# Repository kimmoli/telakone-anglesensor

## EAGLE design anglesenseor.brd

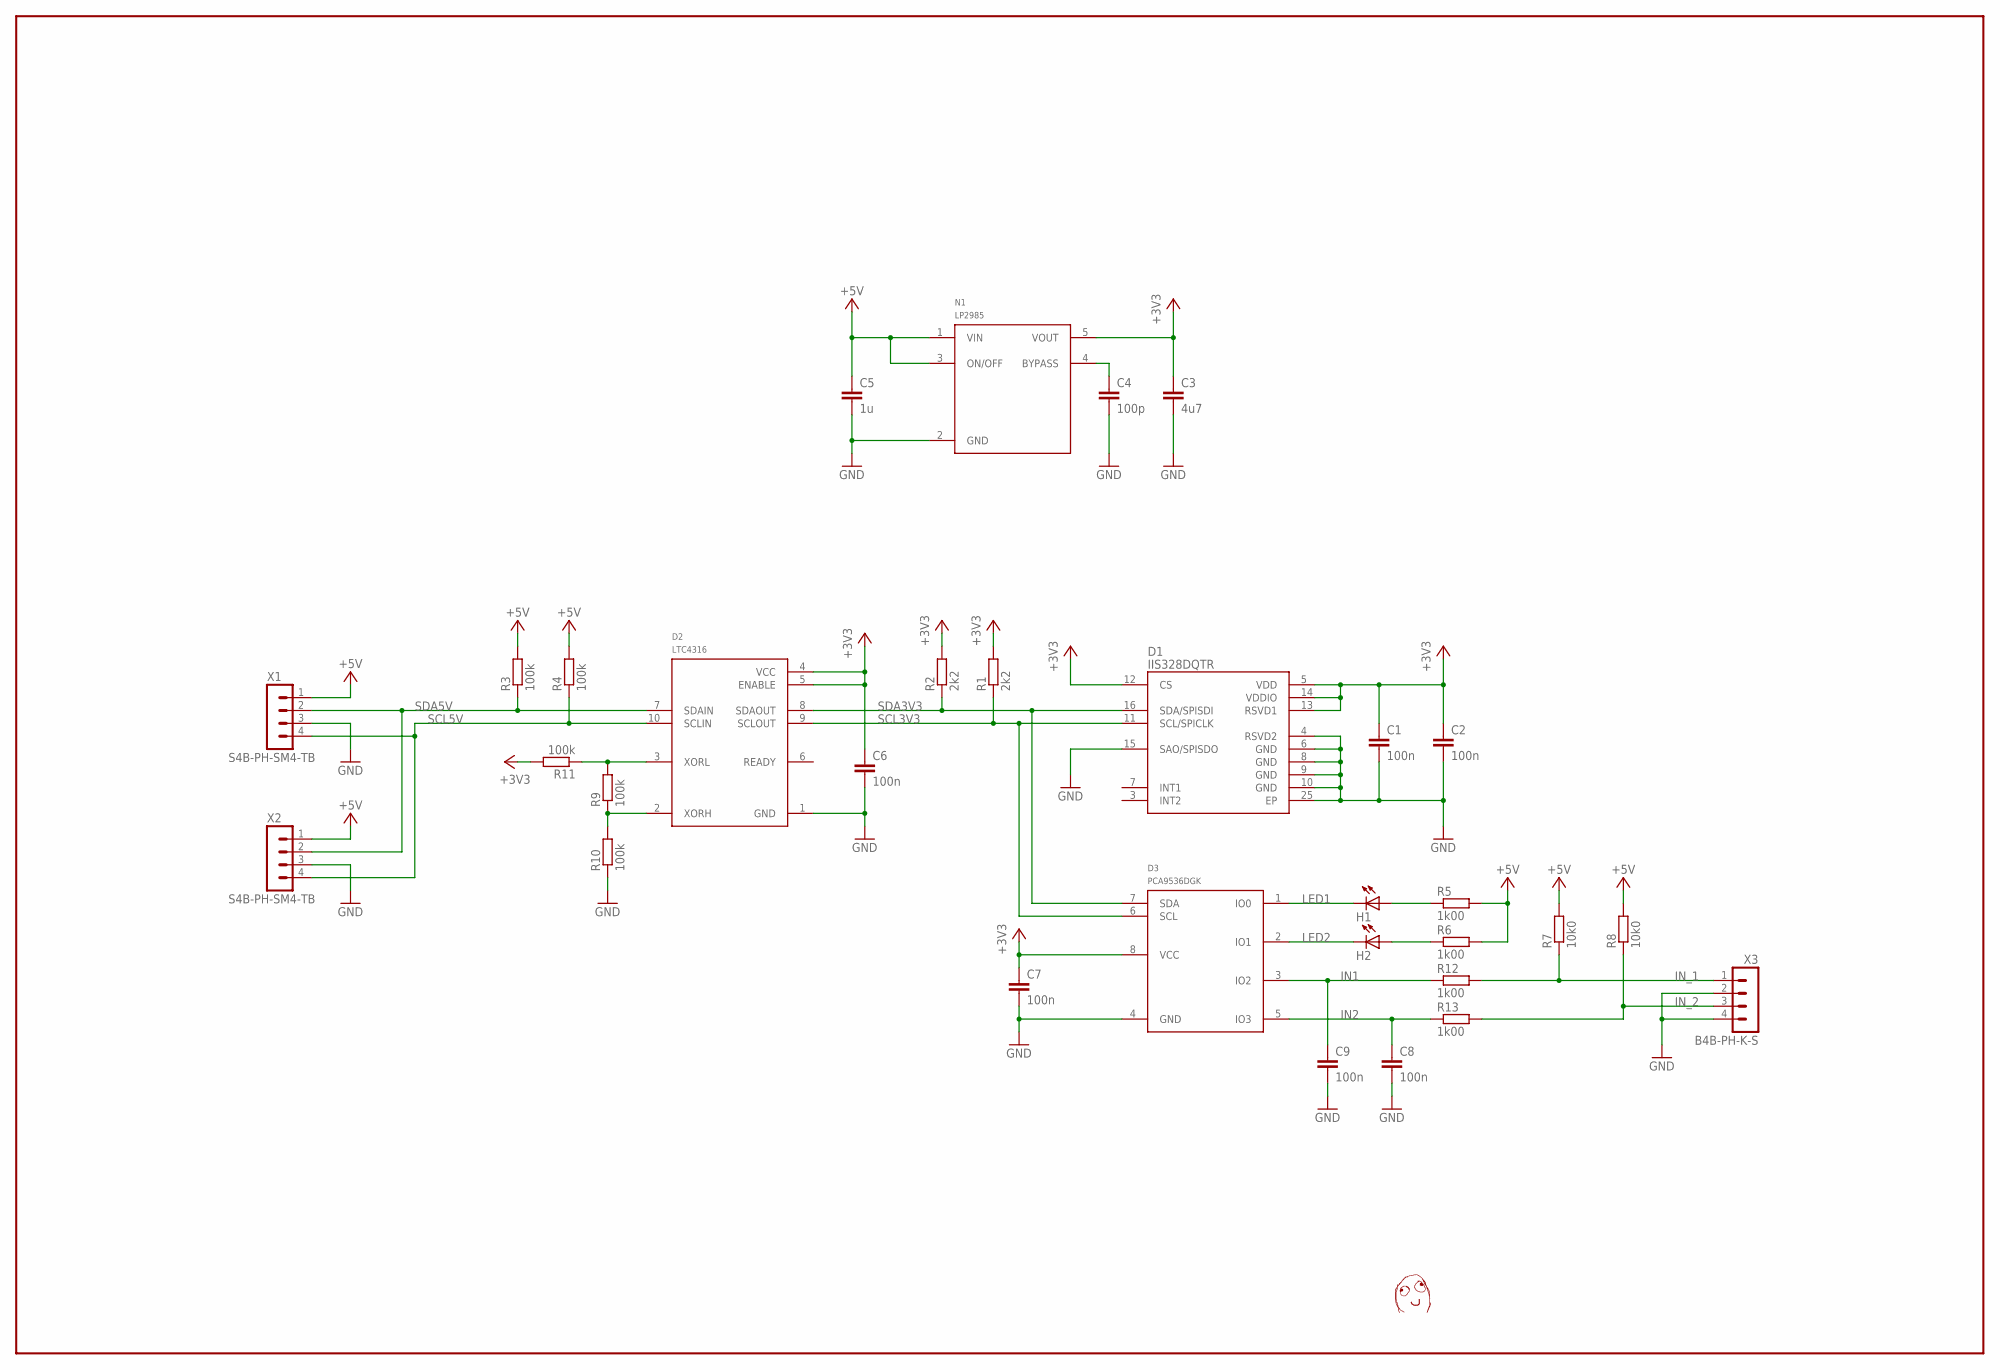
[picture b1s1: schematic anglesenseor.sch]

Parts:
C1, C2, C6, C7, C8, C9: 100n; C0603
C3: 4u7; OMAT_IC_2_C0805
C4: 100p; OMAT_IC_2_C0603
C5: 1u; OMAT_IC_2_C0603
D1: IIS328DQTR; QFN50P400X400X100-25N
D2: LTC4316; MSOP-10
D3: PCA9536DGK; TSSOP8-66
H1, H2: LEDCHIPLED_0603; CHIPLED_0603
N1: LP2985; SOT95P280X145-5N
R1, R2: 2k2; R0603
R3, R4, R9, R10, R11: 100k; R0603
R5, R6, R12, R13: 1k00; R0603
R7, R8: 10k0; R0603
U$1: DAFUG
X1, X2: S4B-PH-SM4-TB; JST-PH2.0-RA-4
X3: B4B-PH-K-S

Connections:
+3V3: C1.1, C2.1, C3.1, C6.1, C7.1, D1.5 (VDD), D1.12 (CS), D1.13 (RSVD1), D1.14 (VDDIO), D2.4 (VCC), D2.5 (ENABLE), D3.8 (VCC), N1.5 (VOUT), R1.2, R2.2, R11.2
+5V: C5.1, N1.1 (VIN), N1.3 (ON/OFF), R3.2, R4.2, R5.2, R6.2, R7.2, R8.2, X1.1, X2.1
GND: C1.2, C2.2, C3.2, C4.2, C5.2, C6.2, C7.2, C8.2, C9.2, D1.4 (RSVD2), D1.6 (GND), D1.8 (GND), D1.9 (GND), D1.10 (GND), D1.15 (SAO/SPISDO), D1.25 (EP), D2.1 (GND), D3.4 (GND), N1.2 (GND), R10.1, X1.3, X2.3, X3.2, X3.4
IN1: C9.1, D3.3 (IO2), R12.1
IN2: C8.1, D3.5 (IO3), R13.1
IN_1: R7.1, R12.2, X3.1
IN_2: R8.1, R13.2, X3.3
LED1: D3.1 (IO0), H1.C
LED2: D3.2 (IO1), H2.C
unnamed: C4.1, N1.4 (BYPASS)
unnamed: D2.3 (XORL), R9.2, R11.1
unnamed: D2.2 (XORH), R9.1, R10.2
unnamed: H2.A, R6.1
unnamed: H1.A, R5.1
SCL3V3: D1.11 (SCL/SPICLK), D2.9 (SCLOUT), D3.6 (SCL), R1.1
SCL5V: D2.10 (SCLIN), R4.1, X1.4, X2.4
SDA3V3: D1.16 (SDA/SPISDI), D2.8 (SDAOUT), D3.7 (SDA), R2.1
SDA5V: D2.7 (SDAIN), R3.1, X1.2, X2.2

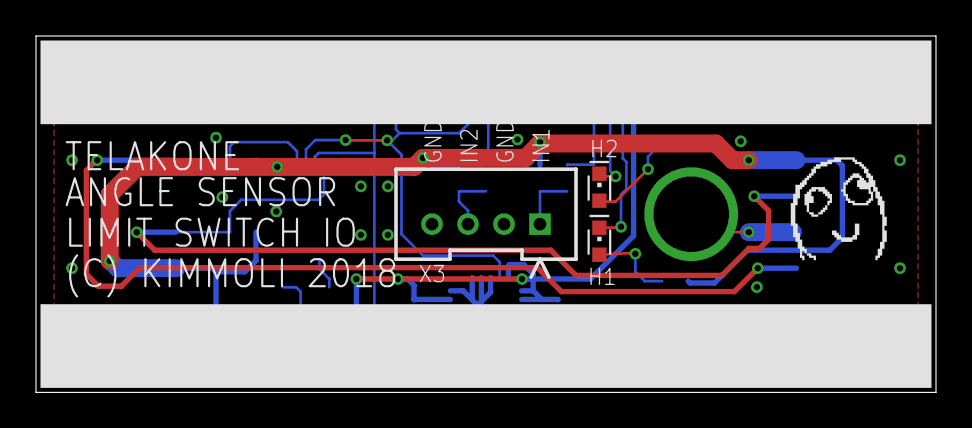
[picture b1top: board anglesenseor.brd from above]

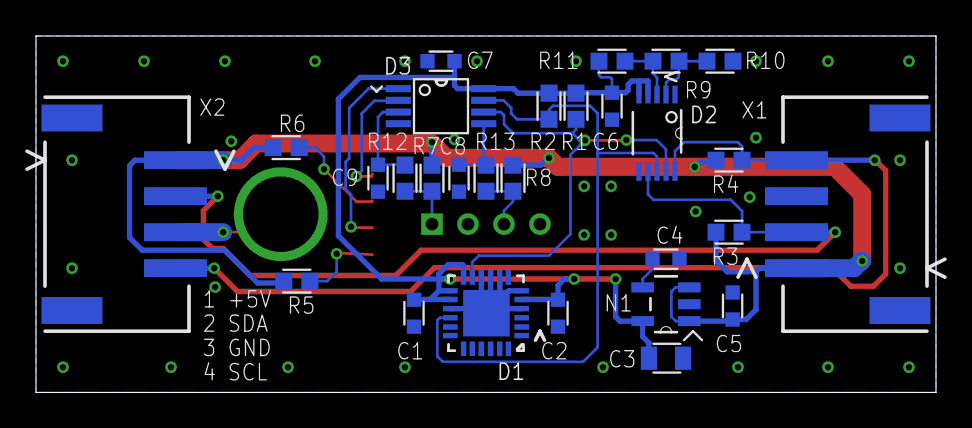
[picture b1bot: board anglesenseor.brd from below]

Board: 2 copper layers, 50.0 x 19.8 mm, 32 parts (28 on the bottom side), 18 nets.

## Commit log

2018-12-15 initial
2018-12-16 routed
2018-12-16 mutteri
2018-12-17 more gnd, finalise
2018-12-17 Add PDF outputs
2018-12-17 translation
